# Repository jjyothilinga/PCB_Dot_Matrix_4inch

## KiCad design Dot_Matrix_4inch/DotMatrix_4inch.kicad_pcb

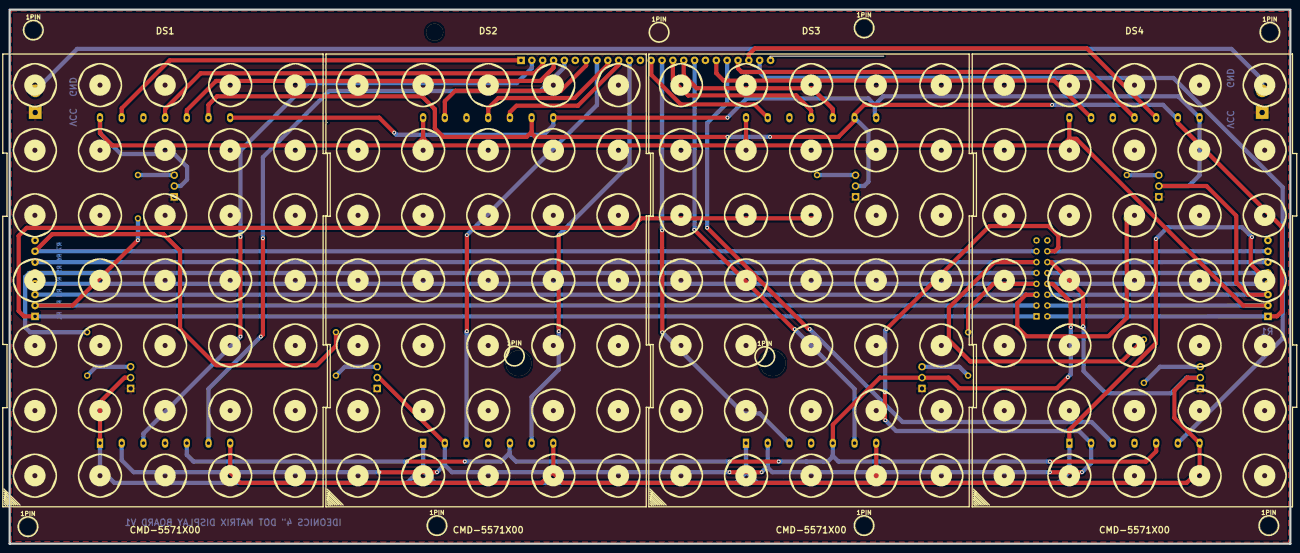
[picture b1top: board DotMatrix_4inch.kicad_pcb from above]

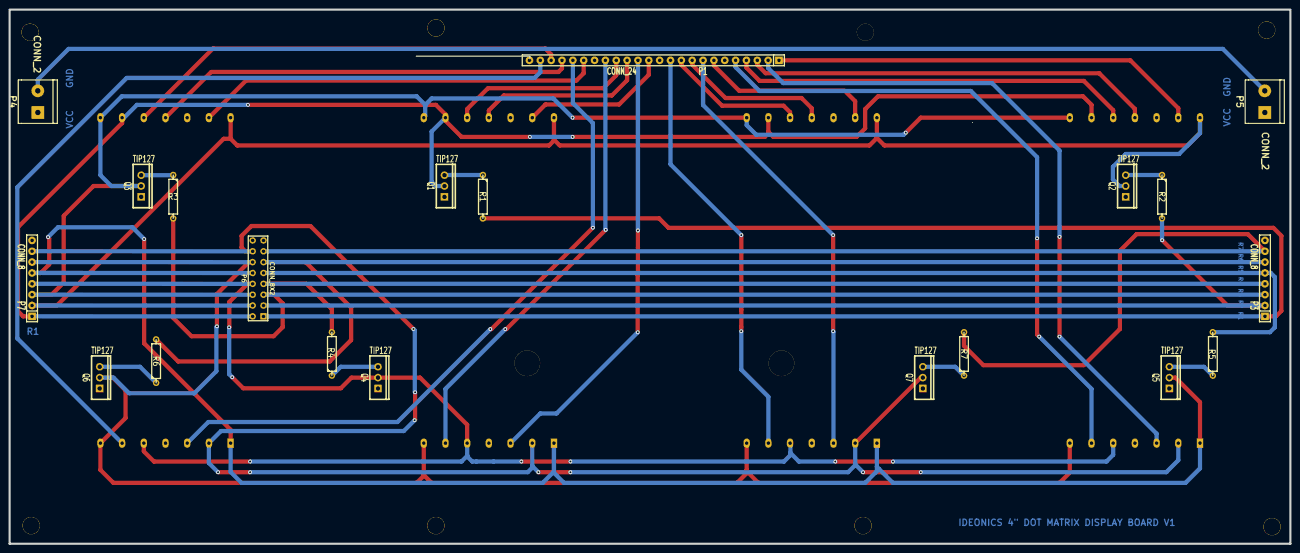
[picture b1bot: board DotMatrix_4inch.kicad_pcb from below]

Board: 2 copper layers, 299.9 x 125.0 mm, 34 parts (20 on the bottom side), 43 nets.

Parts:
1PIN, 1PIN#2, 1PIN#3, 1PIN#4, 1PIN#5, 1PIN#6, 1PIN#7, 1PIN#8, 1PIN#9, 1PIN#10: P***; 1pin
DS1, DS2, DS3, DS4: CMD-5571X00; dotdisp_4_inch
P1: CONN_24; SIL-24
P3, P7: CONN_8; SIL-8
P4, P5: CONN_2; mors_2p
P6: CONN_8X2; pin_array_8x2
Q1, Q2, Q3, Q4, Q5, Q6, Q7: TIP127; TO220_VERT
R1, R2, R3, R4, R5, R6, R7: R; R4

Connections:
/B1: P3.1, P6.1, R1.2
/B2: P3.2, P6.3, R2.2
/B3: P3.3, P6.5, R3.2
/B4: P3.4, P6.7, R4.2
/B5: P3.5, P6.9, R5.2
/B6: P3.6, P6.11, R6.2
/B7: P3.7, P6.13, R7.2
/C1: DS1.13, P1.1
/C2: DS1.3, P1.2
/C3: DS1.11, P1.3
/C4: DS1.10, P1.4
/C5: DS1.6, P1.5
/C6: DS2.13, P1.7
/C7: DS2.3, P1.8
/C8: DS2.11, P1.9
/C9: DS2.10, P1.10
/C10: DS2.6, P1.11
/C11: DS3.13, P1.13
/C12: DS3.3, P1.14
/C13: DS3.11, P1.15
/C14: DS3.10, P1.16
/C15: DS3.6, P1.17
/C16: DS4.13, P1.19
/C17: DS4.3, P1.20
/C18: DS4.11, P1.21
/C19: DS4.10, P1.22
/C20: DS4.6, P1.23
/R1: Q1.1, R1.1
/R2: Q2.1, R2.1
/R3: Q3.1, R3.1
/R4: Q4.1, R4.1
/R5: Q5.1, R5.1
/R6: Q6.1, R6.1
/R7: Q7.1, R7.1
/ROW1: DS1.9, DS2.9, DS3.9, DS4.9, P6.2, P7.1, Q1.2
/ROW2: DS1.14, DS2.14, DS3.14, DS4.14, P6.4, P7.2, Q2.2
/ROW3: DS1.8, DS2.8, DS3.8, DS4.8, P6.6, P7.3, Q3.2
/ROW4: DS1.5, DS2.5, DS3.5, DS4.5, P6.8, P7.4, Q4.2
/ROW5: DS1.1, DS2.1, DS3.1, DS4.1, P6.10, P7.5, Q5.2
/ROW6: DS1.7, DS2.7, DS3.7, DS4.7, P6.12, P7.6, Q6.2
/ROW7: DS1.2, DS2.2, DS3.2, DS4.2, P6.14, P7.7, Q7.2
GND: P4.2, P5.2
VCC: P4.1, P5.1, Q1.3, Q2.3, Q3.3, Q4.3, Q5.3, Q6.3, Q7.3

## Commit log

2015-05-30 :circus_tent: Added .gitattributes & .gitignore files
2015-05-30 Project creation
